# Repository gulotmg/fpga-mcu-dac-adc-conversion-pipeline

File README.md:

# STM32 + FPGA + DAC7311 - 500 kSPS Acquisition & Analysis Pipeline

Acquisition and characterization pipeline built around an STM32 Nucleo-C031C6 and a Spartan-7 SEA/FPGA board. The FPGA design is developed in Vivado as fully custom, synthesizable VHDL. The FPGA drives a TI DAC7311, used at 8-bit code resolution, to generate sine, triangle, and sawtooth waveforms and provides a 500 kHz trigger that hardware-triggers the STM32 ADC via EXTI line 11.

The STM32 firmware is written entirely bare-metal at register level (no HAL), developed in STM32CubeIDE with a 48 MHz system clock: ADC samples are moved by DMA into a 5000-sample buffer and, when the buffer is full, a firmware state machine streams it over UART to a LabVIEW (VISA) host that performs coherent-sampling spectral analysis (SNR / SFDR / SINAD / THD / ENOB) according to IEEE Standard 1241-2023.

The system features end-to-end automation: the LabVIEW host coordinates runtime frequency sweeps by sending 32-bit DDS tuning words over UART to the STM32. The STM32 bridges the tuning word to the Spartan-7 FPGA via SPI, re-arms the DMA channel, and triggers the ADC automatically without requiring manual board resets.

A dedicated analog reconstruction front-end is placed between the DAC output and the ADC input to smooth the staircase steps produced by the zero-order-hold (ZOH) DAC, eliminate out-of-band spectral images, and prevent aliasing artifacts. The repository also provides a comparison between a passive RC reconstruction filter and a custom-designed **4th-Order Active Sallen-Key Low-Pass Filter powered by a custom discrete regulator.**

## Table of Contents

- [Features](#features)
- [Hardware Setup](#hardware-setup)
- [Analog Filter Design](#analog-filter-design)
- [FPGA DDS & Frequency Generation](#fpga-dds--frequency-generation)
- [Measurement Methodology](#measurement-methodology)
- [Experimental Results & Comparative Analysis](#experimental-results--comparative-analysis)
- [Known Limitations & System Interpretation](#known-limitations--system-interpretation)
- [To Do](#to-do)
- [Repository Structure](#repository-structure)
- [Requirements (Reproducibility)](#requirements-reproducibility)
- [How to Clone and Run](#how-to-clone-and-run)
- [References](#references)
- [License](#license)

## Features

- **Automated Frequency Sweep**: LabVIEW host coordinates runtime frequency sweeps by transmitting 32-bit tuning words over UART; STM32 updates the FPGA DDS over SPI1 master mode and re-arms DMA/ADC without requiring manual resets;
- **Runtime SPI Slave DDS Configuration**: Spartan-7 FPGA receives 32-bit tuning words on the fly, updating frequency and phase-aligning the DDS accumulator;
- **FPGA DDS Engine**: Generates sine / triangle / sawtooth waveforms at 8-bit code resolution with a 32-bit phase accumulator for sub-mHz frequency tuning without spectral leakage;
- **500 kHz Hardware Trigger**: EXTI line 11 routed internally as the hardware trigger for the STM32 ADC;
- **12-bit SAR ADC @ 500 kSPS**: DMA-driven circular/linear buffer acquisition (5000 samples);
- **Analog Reconstruction Filter Comparison**:
  - Baseline passive 1st-order RC filter ($f_c \approx 23.1\text{ kHz}$);
  - Upgraded custom **4th-Order Active Sallen-Key Low-Pass Filter ($f_c \approx 79.6\text{ kHz}$, $-80\text{ dB/dec}$ roll-off)** with rail-to-rail Microchip MCP6021 op-amps;
- **Discrete Linear Power Supply (+5.0 V DC)**: Dedicated on-board series pass regulator isolating the analog op-amp power rails from digital switching noise;
- **UART Data Stream**: High-throughput transmission of the full buffer after acquisition (115200 baud);
- **LabVIEW VISA Host**: Real-time spectral analysis, harmonic extraction, and dynamic parameter computation (SNR, SFDR, SINAD, THD, ENOB);
- **Bare-Metal Register-Level Firmware**: Developed without HAL/LL abstractions using official reference manuals (RM0490) and CMSIS headers at 48 MHz;
- **Custom VHDL Design**: Inferred ROM lookup tables (no vendor IP blocks or `.coe` files) implemented on Xilinx Spartan-7 based SEAB (Spartan Edge Accelerator Board);
- **MATLAB Verification**: DDS verification and LUT synthesis scripts in `data/`.

```mermaid
flowchart LR
    LABVIEW["LabVIEW Host<br/>Sweep & IEEE 1241 Metrics"]
    UART["UART Link<br/>PA2 TX / PA3 RX (115200)"]
    MCU["STM32C031C6<br/>ADC1 + DMA1 + SPI1 Master"]
    SPI["SPI Bus<br/>PA5 SCK, PA7 MOSI, PA6 CS"]
    FPGA["Spartan-7 FPGA<br/>DDS + SPI Slave + Trigger"]
    DAC["DAC7311<br/>8-bit"]
    FILTER["Active Sallen-Key Filter<br/>4th-Order / -80 dB/dec"]
    PSU["Discrete Linear PSU<br/>Isolated +5.0 V Rail"]

    LABVIEW -->|4-byte tuning word| UART
    UART --> MCU
    MCU -->|32-bit SPI word| SPI
    SPI --> FPGA
    FPGA -->|8-bit waveform| DAC
    FPGA -.->|500 kHz trigger| MCU
    DAC -->|Analog staircase| FILTER
    PSU -.->|Clean VDD| FILTER
    FILTER -->|Smooth analog signal| MCU
    MCU -->|5000 ADC samples| UART
    UART -->|Serial stream| LABVIEW
```

## Hardware Setup

| Signal | MCU Pin | Spartan-7 SEA Pin | Connector (UM2953) | Firmware Configuration | Note |
|---|---|---|---|---|---|
| **DAC7311 Analog Output (Filtered)** | PA1 - ADC_IN1, CH1 | - | Arduino A1 / morpho 12 | Analog mode; sampling time 12.5 ADC cycles | Signal under test, after reconstruction filter |
| **500 kHz Trigger (FPGA)** | PA11 - EXTI line 11 | N14 (FPGA_IO0) | Arduino A4 / morpho 33 | Digital input, pull-down, rising edge; ADC hardware trigger (EXTSEL = 111, EXTEN = 01) | SEA board trigger output |
| **SPI Chip Select** | PA6 | M14 (FPGA_IO1) | morpho 13 / D12 | Push-pull GPIO output, active-low | Software NSS from MCU to FPGA |
| **SPI Serial Clock** | PA5 - SPI1_SCK | C4 (FPGA_IO2) | morpho 11 / D13 | AF0, SPI1 Master clock | SCLK to FPGA |
| **SPI MOSI** | PA7 - SPI1_MOSI | B13 (FPGA_IO3) | morpho 15 / D11 | AF0, SPI1 Master simplex transmit | 32-bit tuning word data to FPGA |
| **UART TX -> PC** | PA2 - USART2_TX | - | morpho 35 (VCP) | AF1, 115200 8N1, BRR computed @ 48 MHz PCLK | Telemetry stream: 5000 ADC samples |
| **UART RX <- PC** | PA3 - USART2_RX | - | morpho 37 (VCP) | AF1, 115200 8N1, RXNE interrupt enabled | Command reception: 4-byte phase word |
| **GND** | common | GND | - | - | Shared ground plane between SEA board, PCB filter, and Nucleo |

## Analog Filter Design

### - Baseline Reconstruction Low-Pass Filter (Passive RC Prototype)

A passive 1st-order RC low-pass filter was initially placed between the DAC7311 output and the STM32 ADC input to remove high-frequency steps produced by the DAC zero-order-hold behavior, attenuate out-of-band spectral images, and prevent aliasing into the ADC baseband:

- **Resistor**: $\mathbf{220\,\Omega \parallel 100\,\Omega \implies R \approx 68.75\,\Omega}$;
- **Capacitor**: $\mathbf{100\text{ nF}}$ ceramic disc;
- **Cut-off Frequency**: $\mathbf{f_c = \dfrac{1}{2\pi R C} \approx 23.1\text{ kHz}}$.

This cut-off is placed well above the test signal frequencies ($1\text{–}8\text{ kHz}$) and below the $250\text{ kHz}$ Nyquist limit.

*Initial breadboard test bench: Nucleo-C031C6 (left), SEA/FPGA board (right), DAC7311 output probed on CH2; common ground via breadboard. The scope displays the DAC-generated sine wave acquired by the pipeline comparing filtered (blue) and unfiltered (yellow) at 8 kHz.*

### - Upgraded 4th-Order Active Sallen-Key Filter & Discrete Linear Power Supply Design

To overcome the limitations of the passive prototype (limited $-20\text{ dB/decade}$ roll-off, impedance loading of the DAC, and parasitic noise pickup from breadboard), a custom 2-layer hardware PCB was engineered.

#### Subsystem Schematic & Circuit Details

#### Physical Test Bench Setup (Updated Active Filter PCB)

*Updated test bench: Nucleo-C031C6 (top), Spartan-7 SEA FPGA board (bottom-left), and custom Active Filter & Discrete Linear Power Supply PCB (bottom-right). The boards share a common ground, with the DAC output routed through the 4th-order Sallen-Key active filter directly to STM32 ADC PA1 (CH1) and hardware-triggered at 500 kSPS via PA11.*

The board integrates two main sections on a single PCB:
1. **4th-Order Sallen-Key Active Low-Pass Filter**: Cascaded dual 2nd-order unity-gain stages built with low-noise, rail-to-rail Microchip MCP6021 op-amps ($10\text{ MHz}$ GBWP, $8.7\text{ nV}/\sqrt{\text{Hz}}$).
2. **Dedicated Discrete Series Pass Linear Regulator**: A discrete BJT voltage regulator providing an isolated, low-noise supply rail directly to the operational amplifiers.

#### Sallen-Key Filter Frequency Characteristic

The active filter implements a cascaded 4th-order unity-gain Sallen-Key low-pass topology with equal component values ($R = 2.0\text{ k}\Omega$, $C = 1.0\text{ nF}$):

$$\mathbf{f_0 \approx 79.58\text{ kHz}}$$

- **Passband Response ($1\text{–}8\text{ kHz}$)**: Virtually zero amplitude attenuation across the characterization range ($< 0.01\text{ dB}$ at $1\text{ kHz}$ and $< 0.35\text{ dB}$ at $8\text{ kHz}$).
- **Stopband Rejection**: Beyond $f_0$, the filter rolls off at **$-80\text{ dB/decade}$** ($-24\text{ dB/octave}$), strongly suppressing DAC staircase steps and aliasing images around Nyquist ($250\text{ kHz}$) and sampling rate ($500\text{ kSPS}$).

*LTspice AC analysis: Bode magnitude and phase response of the 4th-order Sallen-Key low-pass filter.*

---

#### Filter Power Supply Design Justification

While using an off-the-shelf monolithic LDO (such as an LM317, L7805, or LP2985) would have been more straightforward, designing a custom discrete series pass regulator was deliberately chosen for educational satisfaction since calculating thermal drift compensation, differential error tracking, Miller stability compensation, and foldback current limiting has been more interesting and rewarding. PSRR drops above $10\text{ kHz}$ (falling below $30\text{ dB}$ at $100\text{ kHz}\dots 1\text{ MHz}$) (this is also the reason why datasheets suggest to put a 100 nF capacitor close to the power supply). Since the power supply used (5V from the Nucleo) may generate high-frequency spikes precisely where op-amp PSRR is weakest, a quiet power supply definitely helps keeping supply noise from degrading dynamic spectral measurements of interest.

#### Sizing, Dimensioning & Thermal Compensation Analysis

The discrete regulator topology was sized and analyzed according to classical analog power supply design principles: see [filter/README.md](filter/README.md#discrete-power-supply-design--analysis) for the complete analytical derivations (bandgap reference voltage $\mathbf{V_{ref}}$ and thermal compensation, closed-loop output scaling, Miller compensation, and foldback current limiting).

## FPGA DDS & Frequency Generation

The waveform generator uses a 32-bit Direct Digital Synthesis (DDS) architecture reading from synthesizable inferred ROM lookup tables (256 samples × 8-bit), without vendor IP cores or `.coe` files.

The logic behind this is simple: instead of an 8-bit phase accumulator, we use 32 bits with fixed-point arithmetic. The top 8 bits (integer part) index the 256 samples in the ROM, while the lower 24 bits accumulate the decimal phase increment at each update. Adding a decimal step allows generating precise frequencies without drift.

Each DAC serial frame takes 42 clock cycles at 100 MHz (100 ns / 10 cycles inter-frame SYNC delay as imposed by DAC7311 datasheet + 32 serial clock cycles for 16 bits).

To generate exactly $f_{\text{out}} = 1000.00\text{ Hz}$, the 32-bit tuning word $M$ is calculated as:

$$M = \text{round}\left( \frac{f_{\text{out}} \cdot 42 \cdot 2^{32}}{f_{\text{clk}}} \right) = \text{round}\left( \frac{1000 \cdot 42 \cdot 4\,294\,967\,296}{100\,000\,000} \right) = 1\,803\,886$$

With $M = 1\,803\,886$, the effective output frequency is $999.99985\text{ Hz}$ (error $< 0.0002\text{ Hz}$), preventing phase drift and eliminating spectral leakage.

## Measurement Methodology

The measurement pipeline operates bidirectionally: test frequency is selected from LabVIEW and transmitted via UART to the STM32 Nucleo, which bridges the command via SPI to the Spartan-7 FPGA to update the DDS tuning word in real time before triggering coherent ADC acquisition.

### Coherent Sampling

The spectral analysis relies on **coherent sampling**: the record length $N$ is chosen so that each acquisition contains an **integer number of periods** (exactly 10) of the generated sine wave. This makes the rectangular window exact and completely eliminates spectral leakage.

$$N = 10 \cdot \frac{f_s}{f_{sig}} \qquad \text{with} \quad f_s = 500\text{ kSPS}$$

Sweeping $N$ over the available record lengths yields the following test frequencies (10 periods per record in every case):

| $N$ (samples) | $f_{sig}$ (kHz) | Periods in record |
|:---:|:---:|:---:|
| 5000 | 1 | 10 |
| 2500 | 2 | 10 |
| 1250 | 4 | 10 |
| 625  | 8 | 10 |

For each acquisition, all available harmonics (below Nyquist $f_s/2$) are extracted to calculate SINAD, and the first 10 harmonics are used to compute THD according to IEEE Standard 1241-2023.

*Labview Front Panel showing acquisition and elaboration at 2 kHz.*

### Performance Metrics Definitions

$$\mathrm{SNR} = 20 \log_{10}\left(\frac{V_{fund}}{V_{noise,\mathrm{rms}}}\right) \quad [\mathrm{dB}]$$

$$\mathrm{SFDR} = 20 \log_{10}\left(\frac{V_{fund}}{V_{spur,\mathrm{max}}}\right) \quad [\mathrm{dB}]$$

$$\mathrm{SINAD} = 20 \log_{10}\left(\frac{V_{fund}}{\sqrt{\sum_{h=2}^{N} V_{h}^{2} + V_{noise,\mathrm{rms}}^{2}}}\right) \quad [\mathrm{dB}]$$

$$\mathrm{THD} = 20 \log_{10}\left(\frac{\sqrt{\sum_{h=2}^{10} V_{h}^{2}}}{V_{fund}}\right) \quad [\mathrm{dB}]$$

$$\mathrm{ENOB} = \frac{\mathrm{SINAD} - 1.76}{6.02} \quad [\mathrm{bit}]$$

where:
- $V_{fund}$: RMS amplitude of the fundamental at $f_{sig}$;
- $V_{noise,\mathrm{rms}}$: Total broadband RMS noise floor, integrated via Parseval's theorem (Root-Sum-Square) over the non-signal bins, excluding the fundamental and extracted harmonics (removing DC, fundamental, and 3 bins per harmonic);
- $V_{spur,\mathrm{max}}$: RMS amplitude of the largest spurious component;
- $V_{h}$: RMS amplitude of the $h$-th harmonic, $h = 2 \dots N$.

## Experimental Results & Comparative Analysis

All metrics refer to the **complete signal chain**: DAC7311 + Filter Subsystem + Interconnect + STM32 ADC.

### 1. Baseline Performance: Passive 1st-Order RC Filter

| $N$ | $f_{sig}$ (kHz) | SNR (dB) | SFDR (dB) | SINAD (dB) | THD (dB) | ENOB (bit) |
|:---:|:---:|:---:|:--:|:---:|:---:|:---:|
| 5000 | 1 | 42.6870 | 54.5340 | 40.6990 | −52.7370 | 6.4680 |
| 2500 | 2 | 43.1590 | 49.0060 | 40.4000 | −46.9600 | 6.4190 |
| 1250 | 4 | 41.8920 | 44.6280 | 37.1540 | −40.3040 | 5.8790 |
| 625  | 8 | 43.0420 | 36.3770 | 30.6040 | −31.2060 | 4.7910 |

### 2. Enhanced Performance: 4th-Order Active Sallen-Key Filter & Discrete PSU

| $N$ | $f_{sig}$ (kHz) | SNR (dB) | SFDR (dB) | SINAD (dB) | THD (dB) | ENOB (bit) |
|:---:|:---:|:---:|:--:|:---:|:---:|:---:|
| 5000 | 1 | **52.6060** | **58.4900** | **48.2820** | **−57.0780** | **7.7280** |
| 2500 | 2 | **52.7490** | **54.2650** | **48.4530** | **−52.9190** | **7.7560** |
| 1250 | 4 | **50.8340** | **48.5110** | **45.7280** | **−47.9480** | **7.3040** |
| 625  | 8 | **52.4230** | **42.9030** | **42.2110** | **−42.7230** | **6.7190** |

## Known Limitations & System Interpretation

- **8-bit DAC Resolution and ADC Bottleneck**: The DAC was intentionally operated at 8-bit resolution in an attempt to characterize its baseline performance. Following the fix of a previous conceptual error in the noise RMS computation, the measured SNR ($\approx 52.6\text{–}52.7\text{ dB}$) now possesses sound physical meaning and is likely limited by the 8-bit DAC baseline resolution (theoretical full-scale SNR $\approx 49.92\text{ dB}$). With the 4th-order active filter and clean discrete linear PSU, the measured ENOB at $1\text{ kHz}$ reaches $7.73\text{ bits}$, demonstrating that the signal chain preserves nearly the full theoretical resolution of the DAC. The main issue lies in the fact that in order to correctly evaluate the contribution in the degradation of the performance of the whole system we'd need a golden standard to actually understand to what extent the loss in performance with frequency is related to the DAC. It would be key to first characterize every component of the pipeline with a strong reference; yet it's very likely that the bottleneck of the system is indeed the DAC. 
- **Frequency-Dependent Roll-Off & Phase Increment**: At higher frequencies ($8\text{ kHz}$), the DDS phase step increases, exciting higher-frequency quantization steps. The steep $-80\text{ dB/decade}$ roll-off of the active filter maintains ENOB at $6.72\text{ bits}$, whereas the passive filter degraded to $4.79\text{ bits}$.
- **Solid Ground Plane & Layout Integrity**: The 100% continuous solid ground plane on `B.Cu` with zero routing breaks eliminates ground loop currents between the FPGA, DAC, and ADC.

## To Do

- ✅ **(DONE)** **Full Measurement Pipeline Automation**: Fully automate the end-to-end characterization pipeline directly from LabVIEW by establishing bidirectional communication from the host PC through the STM32 Nucleo to the Spartan-7 FPGA, allowing dynamic run-time frequency selection, automatic record acquisition, and hands-free sweep computation of dynamic metrics. Implemented via USART2 RX interrupt on STM32, SPI1 master to Spartan-7 SPI slave, firmware DMA re-arming, and automated LabVIEW sweep VI.

## Repository Structure

```
├── README.md                     # Main pipeline documentation
├── LICENSE                       # MIT License (Software & Firmware)
├── LICENSE-HARDWARE              # CERN-OHL-P-2.0 License (Hardware designs)
├── docs/                         # Datasheets, manuals, IEEE standards
│   └── references.md             # External documentation and reference links
├── firmware/                     # Bare-metal STM32C031 firmware (ADC, DMA, SPI, UART)
│   └── DMA_nucleoC03_ADC/        # STM32CubeIDE project with register-level C drivers
├── VHDL/                         # Spartan-7 FPGA design (DDS, SPI slave, 500 kHz trigger)
│   └── DAConSEA.srcs/            # Vivado project source, constraints, testbench
├── labview/                      # VISA host receiver and automated sweep VI
├── data/                         # Waveform generator and LUT synthesis scripts
├── filter/                       # Analog front-end & discrete PSU hardware
│   ├── README.md                 # Filter & discrete power supply analytical design
│   ├── BOM_filter.csv            # Bill of Materials (KiCad export)
│   ├── pcb/                      # KiCad project, schematic (.kicad_sch), and layout (.kicad_pcb)
│   └── simulation/               # LTspice circuit (.asc), MCP6021 model (.lib), and PWL stimulus files
└── img/                          # Schematics, 3D PCB renders, test bench photos, and scope captures
```

## Requirements (Reproducibility)

**Hardware**

- STM32 Nucleo-C031C6 development board;
- Seeed Studio Spartan Edge Accelerator (SEA) board (Xilinx Spartan-7) with TI DAC7311;
- **Active Filter & Discrete Linear Power Supply PCB** (2x Microchip MCP6021, 6x 2N2222, 1x 2N3906, 1x Red LED, resistors, electrolytic and ceramic capacitors; see [BOM](filter/BOM_filter.csv)).
- Passive 1st-order RC reconstruction filter ($68.75\,\Omega$, $100\text{ nF}$) for baseline comparison;
- Regulated DC Power Supply (+5.0 V DC or +7.0 V to +12.0 V DC);
- Oscilloscope (for live signal probing);
- USB cables, jumper wires, common ground connection between boards.

**Software & EDA Tools**

- **STM32CubeIDE** (tested with v1.19.0) - bare-metal C compiler and debugger;
- **Xilinx Vivado** ≥ 2019.1 - Spartan-7 VHDL synthesis and bitstream programming;
- **KiCad EDA** ≥ 8.0 / 10.0 (designed in KiCad 10.0.6) - hardware schematic capture and PCB layout;
- **LTspice** (XVII / 24) - analog circuit simulation and AC/transient verification;
- **MATLAB** or **GNU Octave** - DDS LUT generation and verification scripts (`data/WAVE_GEN.m`);
- **LabVIEW** ≥ 2021 SP1 with **NI-VISA** - host acquisition and FFT spectral analysis.

## How to Clone and Run

```bash
git clone https://github.com/gulotmg/fpga-mcu-dac-adc-conversion-pipeline.git
cd fpga-mcu-dac-adc-conversion-pipeline
```

### Execution Steps

1. **Build and Program FPGA**: Open `VHDL/` in Vivado, synthesize the bitstream, and program the Spartan-7 SEA board.
2. **Flash STM32 Firmware**: Open `firmware/DMA_nucleoC03_ADC` in STM32CubeIDE, compile, and flash the Nucleo-C031C6.
3. **Hardware Interconnect**:
   - Connect DAC7311 output from SEA board to `VDAC1` on the Active Filter PCB;
   - Connect `VOUT1` on the Active Filter PCB to Nucleo PA1 (`ADC_IN1`);
   - Connect SEA 500 kHz trigger (`N14`) to Nucleo PA11 (`EXTI11`);
   - Connect Nucleo PA6 (`CS`) to SEA `M14`;
   - Connect Nucleo PA5 (`SCK`) to SEA `C4`;
   - Connect Nucleo PA7 (`MOSI`) to SEA `B13`;
   - Ensure a common GND rail is shared across all three boards;
   - Power the Active Filter PCB via `VCC1` (+5.0 V DC).
4. **Host Spectral Analysis**:
   - Open `labview/Dynamic_parameters_calculator_IEEE.vi` in LabVIEW;
   - Select the Nucleo Virtual COM Port (115200 baud);
   - Run the automated sweep to step frequencies dynamically and observe FFT and IEEE 1241 metrics, or trigger single acquisitions.

## References

- RM0490: STM32C0x1/C0x3 Reference Manual (ADC, DMA, EXTI, USART);
- UM2953: NUCLEO-C031C6 / NUCLEO-C051C8 User Manual;
- Texas Instruments DAC7311 Datasheet: 12-Bit, Low Power, Single-Channel DAC;
- Microchip MCP6021/2/3/4 Datasheet: Rail-to-Rail Input/Output 10 MHz Op-Amps;
- IEEE Std 1241-2023: IEEE Standard for Terminology and Test Methods for Analog-to-Digital Converters;
- TI Application Report SLOA049D: *Active Filter Design Techniques*;
- TI Application Report SBOA226: *Active Low-Pass Filter Design*.

## License

This project is dual-licensed:

- **Software & Firmware** (STM32 bare-metal C drivers, VHDL DDS architecture, LabVIEW VI, MATLAB scripts): licensed under the [MIT License](LICENSE).
- **Hardware & PCB Designs** (`filter/` KiCad schematic, layout, and Bill of Materials): licensed under the [CERN Open Hardware Licence Version 2 - Permissive (CERN-OHL-P-2.0)](LICENSE-HARDWARE).

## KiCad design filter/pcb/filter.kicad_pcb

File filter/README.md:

# filter/ : 4th-Order Active Sallen-Key Low-Pass Filter & Discrete Linear Power Supply

Custom 2-layer hardware PCB engineered to replace the baseline passive RC filter with a 4th-order unity-gain Sallen-Key active low-pass filter ($f_0 \approx 79.58\text{ kHz}$, $-80\text{ dB/decade}$ roll-off) powered by an isolated discrete linear series pass regulator.

Designed in KiCad 10.0.6, simulated in LTspice.

> **Quick Links**: [Bill of Materials (BOM_filter.csv)](BOM_filter.csv) | [KiCad Schematic](pcb/filter.kicad_sch) | [KiCad PCB Layout](pcb/filter.kicad_pcb) | [LTspice Simulation](simulation/filter.asc)

---

## Discrete Power Supply Design & Analysis

While using an off-the-shelf monolithic LDO (such as an LM317, L7805, or LP2985) would have been more straightforward, designing a custom discrete series pass regulator was deliberately chosen for educational satisfaction since calculating thermal drift compensation, differential error tracking, Miller stability compensation, and foldback current limiting has been more interesting and rewarding. PSRR drops above $10\text{ kHz}$ (falling below $30\text{ dB}$ at $100\text{ kHz}\dots 1\text{ MHz}$) (this is also the reason why datasheets suggest to put a 100 nF capacitor close to the power supply). Since the power supply used (5V from the Nucleo) may generate high-frequency spikes precisely where op-amp PSRR is weakest, a quiet power supply definitely helps keeping supply noise from degrading dynamic spectral measurements of interest.

#### Sizing, Dimensioning & Thermal Compensation Analysis

The discrete regulator topology was sized and analyzed according to classical analog power supply design principles:

### A. Bandgap Reference Voltage ($\mathbf{V_{ref}}$ Derivation & Thermal Compensation)

#### 1. Biasing & Core Topology
Red LED $\mathbf{D_1}$ is used as the reference diode in order to drive a constant current generator (PNP transistor $\mathbf{Q_7}$ biased by $\mathbf{R_1 = 330\,\Omega}$, $\mathbf{R_2 = 330\,\Omega}$, $\mathbf{R_3 = 1.0\text{ k}\Omega}$, and bypass capacitor $\mathbf{C_1 = 47\,\mu\text{F}}$) that feeds the reference core. Forward-biased GaAsP red LEDs exhibit a negative forward voltage temperature coefficient ($\mathbf{\approx -2.0\text{ mV/}^\circ\text{C}}$), providing complementary thermal tracking.

The reference core consists of transistors $\mathbf{Q_1, Q_2, Q_3}$ and resistors $\mathbf{R_5 = 1.0\text{ k}\Omega}$, $\mathbf{R_6 = 10.0\text{ k}\Omega}$, $\mathbf{R_7 = 470\,\Omega}$:
- **Diode-connected $\mathbf{Q_2}$**: carries current $\mathbf{I_1}$ through collector resistor $\mathbf{R_5}$;
- **Degenerated $\mathbf{Q_1}$**: carries current $\mathbf{I_2}$ through collector resistor $\mathbf{R_6}$, with emitter degeneration resistor $\mathbf{R_7}$;
- **Feedback $\mathbf{Q_3}$**: base driven by the collector of $\mathbf{Q_1}$, emitter grounded, and collector tied to node $\mathbf{V_{ref}}$.

#### 2. Analytical Derivation
Neglecting base currents ($\mathbf{I_2 \approx I_{C(Q1)} \approx I_{E(Q1)}}$), the difference in base-emitter voltages appears directly across emitter degeneration resistor $\mathbf{R_7}$:

$$\mathbf{V_{BE(Q2)} - V_{BE(Q1)} = I_{E(Q1)} R_7 \cong I_2 R_7}$$

Using the fundamental BJT exponential relationship $\mathbf{I_C = I_S e^{V_{BE}/V_T} \implies V_{BE} = V_T \ln(I_C / I_S)}$, with thermal voltage $\mathbf{V_T = \frac{kT}{q} \approx 25.86\text{ mV}}$ (at $\mathbf{T = 300\text{ K}}$):

$$\mathbf{V_{BE(Q2)} - V_{BE(Q1)} = \frac{kT}{q} \left[ \ln\left(\frac{I_{C(Q2)}}{I_S}\right) - \ln\left(\frac{I_{C(Q1)}}{I_S}\right) \right] = \frac{kT}{q} \ln\left(\frac{I_1}{I_2}\right) = I_2 R_7}$$

Because $\mathbf{V_{BE(Q2)} \approx V_{BE(Q3)}}$, the voltage drops across the two collector load resistors balance ($\mathbf{I_1 R_5 \approx I_2 R_6 \implies \frac{I_1}{I_2} \approx \frac{R_6}{R_5}}$). Solving for the Proportional To Absolute Temperature (PTAT) current $\mathbf{I_2}$:

$$\mathbf{I_2 = \frac{1}{R_7} \frac{kT}{q} \ln\left(\frac{R_6}{R_5}\right)}$$

The reference voltage at node $\mathbf{V_{ref}}$ is taken at the collector of feedback transistor $\mathbf{Q_3}$:

$$\mathbf{V_{ref} = I_2 R_6 + V_{BE(Q3)} = V_{BE(Q3)} + \frac{R_6}{R_7} \frac{kT}{q} \ln\left(\frac{R_6}{R_5}\right)}$$

#### 3. Numerical Evaluation
Substituting circuit component values ($\mathbf{R_5 = 1.0\text{ k}\Omega}$, $\mathbf{R_6 = 10.0\text{ k}\Omega}$, $\mathbf{R_7 = 470\,\Omega}$, $\mathbf{V_T \approx 25.86\text{ mV}}$, and $\mathbf{V_{BE(Q3)} \approx 0.65\text{ V}}$):

$$\mathbf{\frac{R_6}{R_5} = \frac{10\text{ k}\Omega}{1.0\text{ k}\Omega} = 10 \implies \ln(10) \approx 2.303, \qquad \frac{R_6}{R_7} = \frac{10\,000\,\Omega}{470\,\Omega} \approx 21.28}$$

$$\mathbf{V_{ref} \approx 0.65\text{ V} + 21.28 \times 25.86\text{ mV} \times 2.303 \approx 0.65\text{ V} + 1.267\text{ V} \approx 1.92\text{ V}}$$

#### 4. Thermal Drift Compensation
The temperature variation of the reference voltage is expressed as:

$$\mathbf{\Delta V_{ref} = \Delta V_{BE(Q3)} + \frac{R_6}{R_7} \frac{k\,\Delta T}{q} \ln\left(\frac{R_6}{R_5}\right)}$$

The negative temperature coefficient of $\mathbf{V_{BE(Q3)}}$ ($\mathbf{\approx -2.2\text{ mV/}^\circ\text{C}}$) is compensated by the positive temperature coefficient of the PTAT voltage term, minimizing thermal drift across temperature.

Since the circuit includes foldback short-circuit protection but no overvoltage clamp (for design simplicity), it is strongly recommended not to exceed $\mathbf{+10\text{ V}}$ DC supply to protect the components.

### B. Closed-Loop Output Voltage Scaling

The feedback divider formed by $\mathbf{R_{10} = 1.0\text{ k}\Omega}$ and $\mathbf{R_{11} = 2.0\text{ k}\Omega}$ compares the output voltage against the error amplifier base-emitter junction and reference voltage ($\mathbf{V_{BE(Q5)} + V_{ref}}$):

$$\mathbf{V_{\text{feedback}} = V_O \cdot \frac{R_{11}}{R_{10} + R_{11}} = V_O \cdot \frac{2.0\text{ k}\Omega}{1.0\text{ k}\Omega + 2.0\text{ k}\Omega} = \frac{2}{3} V_O \equiv V_{BE(Q5)} + V_{ref}}$$

$$\mathbf{V_{O,\text{ideal}} = (V_{BE(Q5)} + V_{ref}) \cdot \left( 1 + \frac{R_{10}}{R_{11}} \right) = 1.5 \cdot (V_{BE(Q5)} + V_{ref})}$$

Using $\mathbf{V_{ref} \approx 1.92\text{ V}}$ calculated above and nominal $\mathbf{V_{BE(Q5)} \approx 0.65\text{ V}}$:

$$\mathbf{V_{O,\text{ideal}} = 1.5 \cdot (0.65\text{ V} + 1.92\text{ V}) = 1.5 \cdot 2.57\text{ V} \approx 3.86\text{ V}}$$

### C. Loop Stability & Miller Compensation

To guarantee unconditional stability under reactive loads, capacitor $\mathbf{C_5 = 1.0\text{ nF}}$ is placed across the collector-base junction of pass driver $\mathbf{Q_5}$. Via the Miller effect, the equivalent capacitance seen at the driver base is multiplied by the stage voltage gain:

$$\mathbf{C_{\text{Miller}} = C_5 \cdot (1 + |A_v|)}$$

This creates a dominant low-frequency pole, rolling off loop gain well before parasitic phase shifts from the series pass transistor $\mathbf{Q_4}$ and output decoupling capacitors can degrade phase margin, ensuring a stable power supply and preventing potential oscillations.

### D. Foldback Current Limiting

Resistor $\mathbf{R_{sense} = 10\,\Omega}$ senses the load current $\mathbf{I_L}$ delivered by series pass transistor $\mathbf{Q_4}$. A resistive divider formed by $\mathbf{R_{F1} = R_{14} = 220\,\Omega}$ and $\mathbf{R_{F2} = R_{15} = 1.0\text{ k}\Omega}$ biases sense transistor $\mathbf{Q_6}$ (2N2222), whose emitter is tied to $\mathbf{V_O}$:

$$\mathbf{V_{BE, Q6} = (V_O + I_L R_{sense}) \frac{R_{F2}}{R_{F1} + R_{F2}} - V_O}$$

Imposing $\mathbf{V_{BE, Q6} = 0.6\text{ V}}$ at the activation threshold gives:

$$\mathbf{0.6\text{ V} = (V_O + I_{th} R_{sense}) \frac{R_{F2}}{R_{F1} + R_{F2}} - V_O}$$

Solving for the threshold current $\mathbf{I_{th}}$:

$$\mathbf{I_{th} = \frac{0.6\text{ V}}{R_{sense}} \left( 1 + \frac{R_{F1}}{R_{F2}} \right) + \frac{V_O}{R_{sense}} \left( \frac{R_{F1}}{R_{F2}} \right)}$$

Under dead short-circuit conditions ($\mathbf{V_O = 0\text{ V}}$), the output current folds back to:

$$\mathbf{I_{sc} = \frac{0.6\text{ V}}{R_{sense}} \left( 1 + \frac{R_{F1}}{R_{F2}} \right) = \frac{0.6\text{ V}}{10\,\Omega} \left( 1 + \frac{220\,\Omega}{1000\,\Omega} \right) = 73.2\text{ mA}}$$

Substituting $\mathbf{V_{O,\text{ideal}} \approx 3.86\text{ V}}$ obtained from the bandgap reference and closed-loop scaling equations, the current threshold before regulation drop is:

$$\mathbf{I_{th} = 73.2\text{ mA} + \frac{3.86\text{ V}}{10\,\Omega} \left( \frac{220\,\Omega}{1000\,\Omega} \right) = 73.2\text{ mA} + 84.9\text{ mA} \approx 158.1\text{ mA}}$$

When load current exceeds $\mathbf{I_{th}}$, $\mathbf{Q_6}$ conducts and shunts base drive current away from driver $\mathbf{Q_5}$ and series pass $\mathbf{Q_4}$, folding back the output current from $\mathbf{I_{th} \approx 158.1\text{ mA}}$ down to $\mathbf{I_{sc} \approx 73.2\text{ mA}}$. This limits the maximum short-circuit power dissipation to:

$$\mathbf{P_{diss,\max} = V_{IN} \cdot I_{sc} = 5.0\text{ V} \times 73.2\text{ mA} \approx 366\text{ mW}}$$

protecting the series pass transistor from thermal runaway.

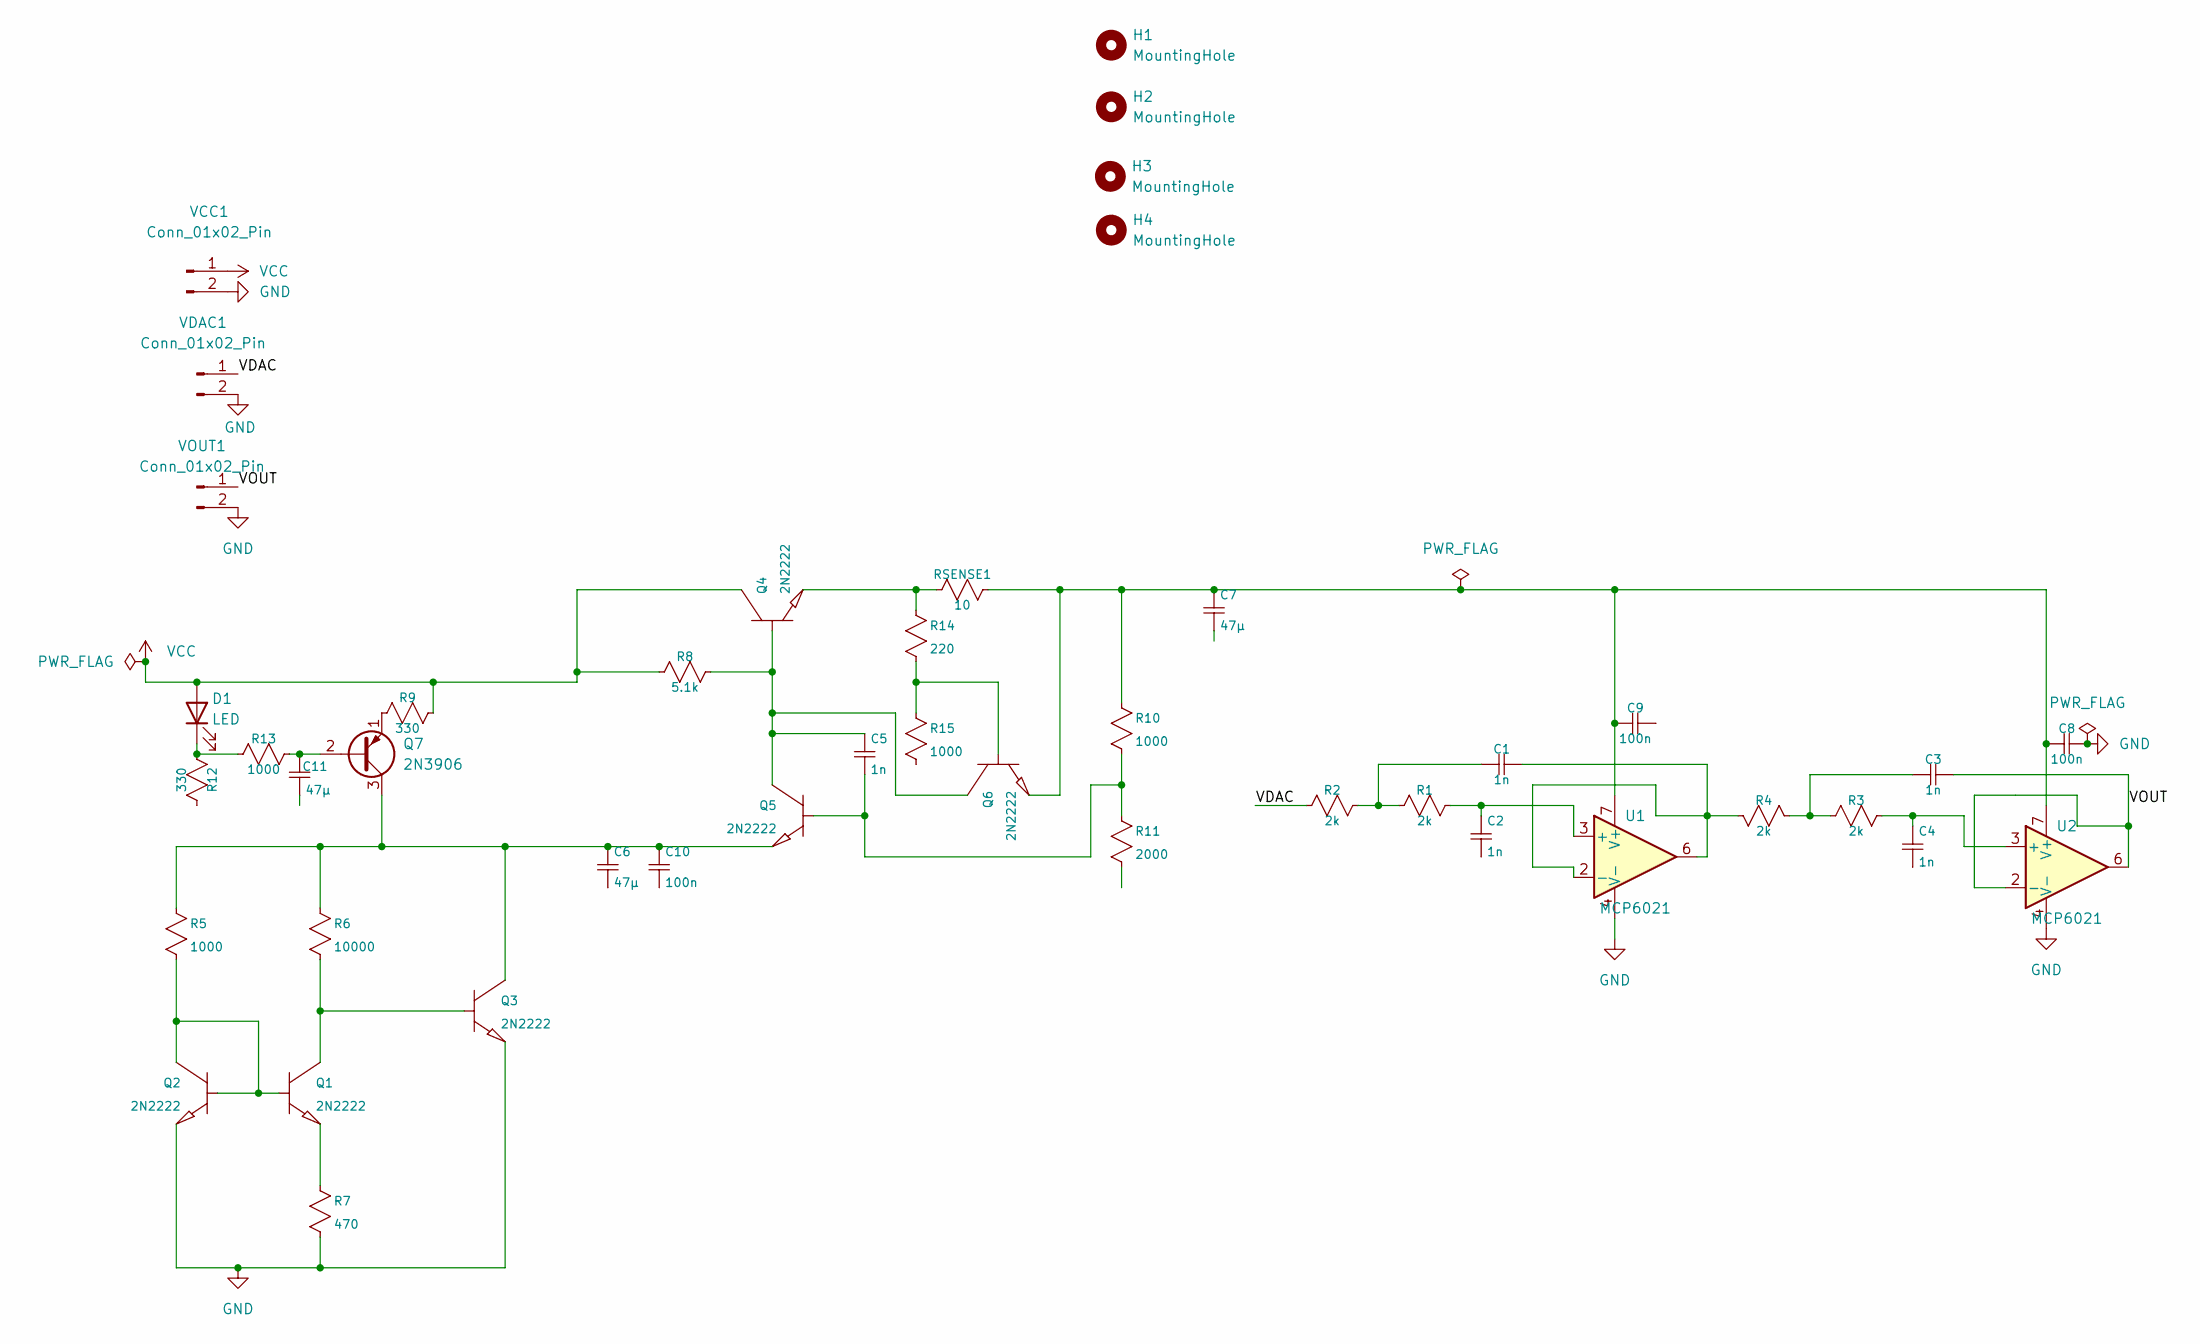
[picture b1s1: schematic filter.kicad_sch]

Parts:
C1, C2, C3, C4, C5: 1n; C_Disc_D5.0mm_W2.5mm_P5.00mm
C6, C7, C11: 47µ; CP_Radial_D4.0mm_P1.50mm
C8, C9, C10: 100n; C_Disc_D5.0mm_W2.5mm_P5.00mm
D1: LED; LED_D4.0mm
H1, H2, H3, H4: MountingHole; MountingHole_3.2mm_M3_Pad
Q1, Q2, Q3, Q4, Q5, Q6: 2N2222; TO-92Flat
Q7: 2N3906; TO-92_Inline
R1, R2, R3, R4: 2k; R_Axial_DIN0204_L3.6mm_D1.6mm_P5.08mm_Horizontal
R5, R10, R13, R15: 1000; R_Axial_DIN0204_L3.6mm_D1.6mm_P5.08mm_Horizontal
R6: 10000; R_Axial_DIN0204_L3.6mm_D1.6mm_P5.08mm_Horizontal
R7: 470; R_Axial_DIN0204_L3.6mm_D1.6mm_P5.08mm_Horizontal
R8: 5.1k; R_Axial_DIN0204_L3.6mm_D1.6mm_P5.08mm_Horizontal
R9, R12: 330; R_Axial_DIN0204_L3.6mm_D1.6mm_P5.08mm_Horizontal
R11: 2000; R_Axial_DIN0204_L3.6mm_D1.6mm_P5.08mm_Horizontal
R14: 220; R_Axial_DIN0204_L3.6mm_D1.6mm_P5.08mm_Horizontal
RSENSE1: 10; R_Axial_DIN0204_L3.6mm_D1.6mm_P5.08mm_Horizontal
U1, U2: MCP6021; DIP-8_W7.62mm
VCC1: Conn_01x02_Pin; PinHeader_1x02_P2.54mm_Vertical
VDAC1: Conn_01x02_Pin; PinHeader_1x02_P2.54mm_Vertical
VOUT1: Conn_01x02_Pin; PinHeader_1x02_P2.54mm_Vertical

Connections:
/VDAC: R2.2, VDAC1.1
/VOUT: C3.1, U2.2 (-), U2.6, VOUT1.1
GND: C2.2, C4.2, C6.2, C7.2, C8.1, C9.1, C10.2, C11.2, Q2.3 (E), Q3.3 (E), R7.2, R11.2, R12.1, R15.2, U1.4 (V-), U2.4 (V-), VCC1.2, VDAC1.2, VOUT1.2
unnamed: C1.2, R1.2, R2.1
unnamed: C3.2, R3.2, R4.2
unnamed: D1.1 (K), R12.2, R13.2
unnamed: Q1.2 (B), Q2.1 (C), Q2.2 (B), R5.2
unnamed: Q1.1 (C), Q3.2 (B), R6.2
unnamed: Q1.3 (E), R7.1
unnamed: C6.1, C10.1, Q3.1 (C), Q5.3 (E), Q7.3 (C), R5.1, R6.1
unnamed: C5.1, Q4.2 (B), Q5.1 (C), Q6.1 (C), R8.1
unnamed: Q4.3 (E), R14.1, RSENSE1.2
unnamed: C5.2, Q5.2 (B), R10.2, R11.1
unnamed: Q6.2 (B), R14.2, R15.1
unnamed: C7.1, C8.2, C9.2, Q6.3 (E), R10.1, RSENSE1.1, U1.7 (V+), U2.7 (V+)
unnamed: C11.1, Q7.2 (B), R13.1
unnamed: Q7.1 (E), R9.2
unnamed: C2.1, R1.1, U1.3 (+)
unnamed: C1.1, R4.1, U1.2 (-), U1.6
unnamed: C4.1, R3.1, U2.3 (+)
VCC: D1.2 (A), Q4.1 (C), R8.2, R9.1, VCC1.1

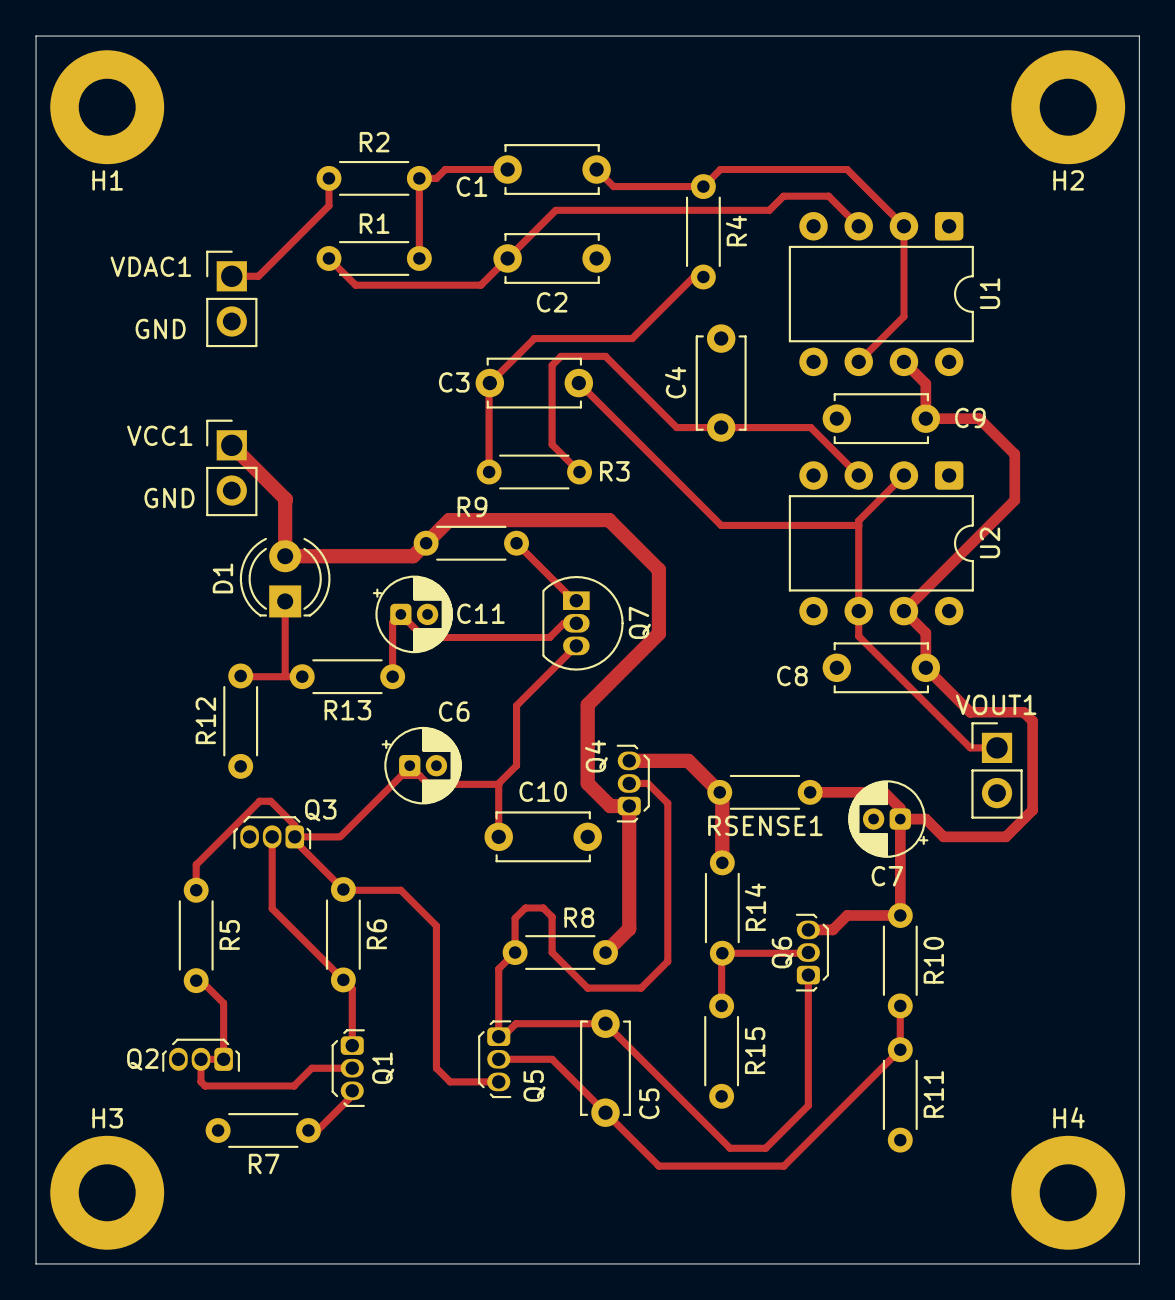
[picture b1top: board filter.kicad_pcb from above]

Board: 2 copper layers, 62.0 x 69.0 mm, 44 parts (0 on the bottom side), 21 nets.

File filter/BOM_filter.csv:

"Refs","Value","Footprint","Qty","DNP"
"C1-C5","1n","Capacitor_THT:C_Disc_D5.0mm_W2.5mm_P5.00mm","5",""
"C6,C7,C11","47µ","Capacitor_THT:CP_Radial_D4.0mm_P1.50mm","3",""
"C8-C10","100n","Capacitor_THT:C_Disc_D5.0mm_W2.5mm_P5.00mm","3",""
"D1","LED","LED_THT:LED_D4.0mm","1",""
"Q1-Q6","2N2222","Package_TO_SOT_THT:TO-92Flat","6",""
"Q7","2N3906","Package_TO_SOT_THT:TO-92_Inline","1",""
"R1-R4","2k","Resistor_THT:R_Axial_DIN0204_L3.6mm_D1.6mm_P5.08mm_Horizontal","4",""
"R5,R10,R13,R15","1000","Resistor_THT:R_Axial_DIN0204_L3.6mm_D1.6mm_P5.08mm_Horizontal","4",""
"R6","10000","Resistor_THT:R_Axial_DIN0204_L3.6mm_D1.6mm_P5.08mm_Horizontal","1",""
"R7","470","Resistor_THT:R_Axial_DIN0204_L3.6mm_D1.6mm_P5.08mm_Horizontal","1",""
"R8","5.1k","Resistor_THT:R_Axial_DIN0204_L3.6mm_D1.6mm_P5.08mm_Horizontal","1",""
"R9,R12","330","Resistor_THT:R_Axial_DIN0204_L3.6mm_D1.6mm_P5.08mm_Horizontal","2",""
"R11","2000","Resistor_THT:R_Axial_DIN0204_L3.6mm_D1.6mm_P5.08mm_Horizontal","1",""
"R14","220","Resistor_THT:R_Axial_DIN0204_L3.6mm_D1.6mm_P5.08mm_Horizontal","1",""
"RSENSE1","10","Resistor_THT:R_Axial_DIN0204_L3.6mm_D1.6mm_P5.08mm_Horizontal","1",""
"U1,U2","MCP6021","Package_DIP:DIP-8_W7.62mm","2",""
"VCC1,VDAC1,VOUT1","Conn_01x02_Pin","Connector_PinHeader_2.54mm:PinHeader_1x02_P2.54mm_Vertical","3",""
